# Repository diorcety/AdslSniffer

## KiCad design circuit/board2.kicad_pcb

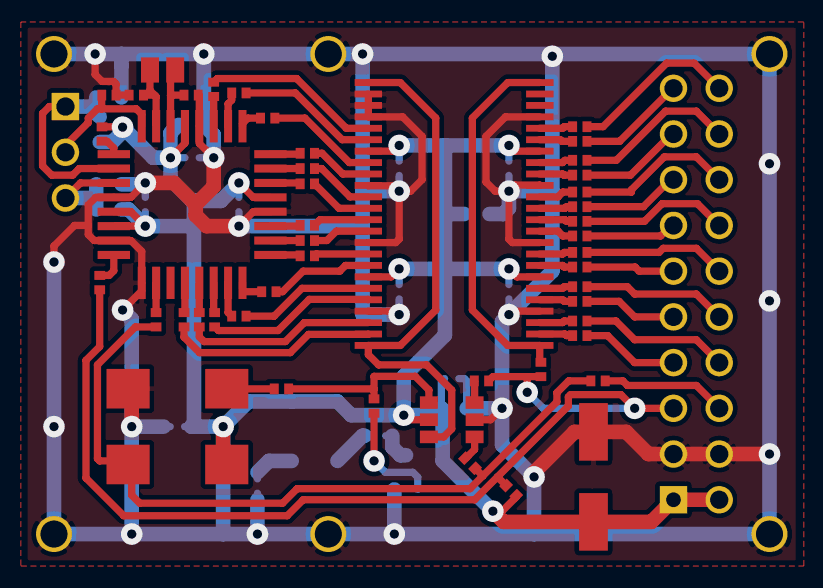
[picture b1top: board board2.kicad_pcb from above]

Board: 2 copper layers, 71 parts (0 on the bottom side), 79 nets.

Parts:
C1, C2, C3, C5, C6, C7, C8, C9, C10, C11, C12, C13: 100n; SM0402
C4, C15, C16, C18, C19: 10u; SM0805
C20: 100u; ESMT18
D1: LED PW; SM1206POL
D2: LED EN; SM1206POL
D3, D4, D5, D6: 3.3V; SOD523
P3: CONN_3; PIN_ARRAY_3X1
P4: CONN_20; pin_array_10x2
Q1: MOS_N; SOT323
R5, R47: 1k; SM0402
R6, R7, R8, R9, R10, R11, R12, R13, R14, R15, R16, R17, R18, R19: 33; SM0402
R20, R22, R23, R24, R25, R26, R46: 49; SM0402
R21, R30, R31, R32, R33, R34, R35, R36, R37, R38, R39, R40, R41, R42, R43: 100; SM0402
R44, R45: 47; SM0402
U1: ADC14L020; LQFP32
U2: 74L2G04; SOT23_6
U3: 74LS162374; SSOP48
X1: CMOS_OSCI; Sit7x5

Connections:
+3.3V: C5.1, C6.1, C7.1, C8.1, C9.1, C10.1, C11.1, C12.1, C13.1, C15.1, C16.1, C18.1, C19.1, C20.1, D1.1, D2.1, D3.2, D5.2, P4.1, P4.2, R5.2, R47.1, U1.5, U1.6, U1.21, U1.29, U2.5, U3.7, U3.18, U3.31, U3.42, X1.4
/CLK: P4.6, R21.1
/L_ENABLE: P4.5, R22.1, R23.1, R24.1, R47.2
GND: C1.2, C2.2, C3.2, C5.2, C6.2, C7.2, C8.2, C9.2, C10.2, C11.2, C12.2, C13.2, C15.2, C16.2, C18.2, C19.2, C20.2, D4.1, D6.1, P4.3, P4.4, Q1.S, R45.2, U1.4, U1.7, U1.9, U1.20, U1.28, U2.2, U3.4, U3.10, U3.15, U3.21, U3.26, U3.27, U3.28, U3.34, U3.39, U3.45, X1.2
unnamed: P4.12, R35.1
unnamed: P4.10, R33.1
unnamed: P4.20, R43.1
unnamed: P4.11, R34.1
unnamed: P4.13, R36.1
unnamed: P4.14, R37.1
unnamed: P4.15, R38.1
unnamed: P4.16, R39.1
unnamed: P4.17, R40.1
unnamed: P4.18, R41.1
unnamed: P4.19, R42.1
unnamed: P4.9, R32.1
unnamed: P4.8, R31.1
unnamed: P4.7, R30.1
unnamed: R25.2, R46.2, U2.4
unnamed: Q1.G, R46.1
unnamed: Q1.D, R44.1
unnamed: D1.2, R45.1
unnamed: D2.2, R44.2
unnamed: R5.1, U1.1
unnamed: R23.2, U2.3
unnamed: R22.2, U1.8
unnamed: R20.2, U1.10
unnamed: R25.1, X1.1
unnamed: R11.2, U1.17
unnamed: R16.2, U1.24
unnamed: R15.2, U1.23
unnamed: R14.2, U1.22
unnamed: R13.2, U1.19
unnamed: R12.2, U1.18
unnamed: R10.2, U1.16
unnamed: R9.2, U1.15
unnamed: R8.2, U1.14
unnamed: R7.2, U1.13
unnamed: C3.1, C4.1, U1.30
unnamed: R30.2, U3.2
unnamed: R31.2, U3.3
unnamed: R32.2, U3.5
unnamed: R33.2, U3.6
unnamed: R26.1, U2.1
unnamed: U2.6, U3.25, U3.48
unnamed: R34.2, U3.8
unnamed: R7.1, U3.46
unnamed: R41.2, U3.17
unnamed: R13.1, U3.37
unnamed: R12.1, U3.38
unnamed: R42.2, U3.19
unnamed: R14.1, U3.36
unnamed: R6.1, U3.47
unnamed: R6.2, U1.12
unnamed: R19.1, U3.29
unnamed: R19.2, U1.27
unnamed: R18.2, U1.26
unnamed: R17.2, U1.25
unnamed: R35.2, U3.9
unnamed: R43.2, U3.20
unnamed: R18.1, U3.30
unnamed: R11.1, U3.40
unnamed: R36.2, U3.11
unnamed: R10.1, U3.41
unnamed: R37.2, U3.12
unnamed: R17.1, U3.32
unnamed: R38.2, U3.13
unnamed: R16.1, U3.33
unnamed: R9.1, U3.43
unnamed: R39.2, U3.14
unnamed: R8.1, U3.44
unnamed: R15.1, U3.35
unnamed: R40.2, U3.16
unnamed: R24.2, U3.1, U3.24
unnamed: R20.1, R21.2, R26.2, X1.3
unnamed: C1.1, P3.2, U1.32
unnamed: C2.1, C4.2, U1.31
unnamed: D3.1, D4.2, P3.1, U1.2
unnamed: D5.1, D6.2, P3.3, U1.3

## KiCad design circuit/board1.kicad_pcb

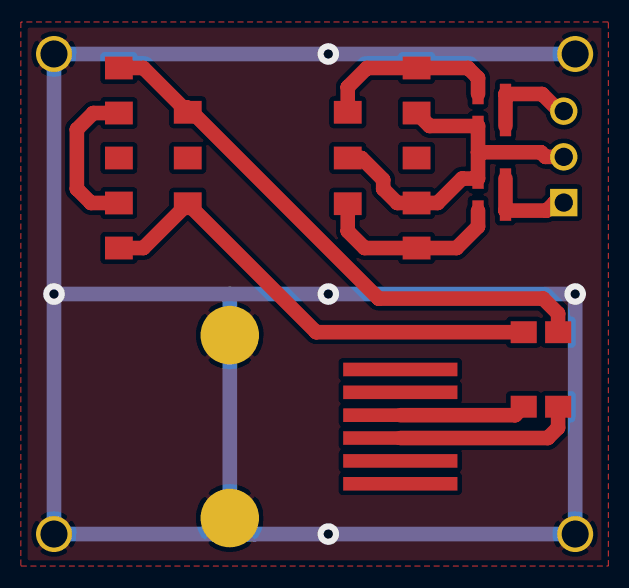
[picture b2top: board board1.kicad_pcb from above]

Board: 2 copper layers, 9 parts (0 on the bottom side), 11 nets.

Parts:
P1: RJ12; RJ11SMT
P2: CONN_3; PIN_ARRAY_3X1
R1, R2: 8k25; SM0603
R3, R4: 1k1; SM0603
T1: B0727-BL
T2: 1812DPS
T3: PWB2010L; PWB2010LB

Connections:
AGND: P1.7, P1.8
unnamed: P2.1, R2.2, R4.1
unnamed: R1.1, T1.6, T3.6
unnamed: R2.1, T1.10, T3.4
unnamed: P1.4, T2.4
unnamed: P2.3, R1.2, R3.1
unnamed: T1.2, T1.4
unnamed: T1.1, T2.3, T3.3
unnamed: P1.3, T2.1
unnamed: T1.5, T2.2, T3.1
unnamed: P2.2, R3.2, R4.2, T1.7, T1.9, T3.5

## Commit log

2012-01-12 Alignement connecteurs
2012-01-12 Correction positions resitances ADC
2012-01-13 Amelioration Schema
2012-01-31 Correction empreinte C4
2012-12-30 Utilise des connecteurs traversant (moins cher)
2012-12-30 Modifie l'emplacement et le net de P6
2012-12-30 Fix DRC
2012-12-30 Ajoute leds
2012-12-30 Ajoute condensateur 10u a chaque composant
2012-12-30 Corrige nom et ajoute csv des composants
2012-12-30 Ajoute transistor pour led en
2012-12-30 Ajout d'une resistance de pull-up pour EN
2012-12-30 Met le COMMON de V+ et V- au milieu
2012-12-31 Corrige empreintes/3D
2012-12-31 Recentre les circuits
2012-12-31 Reduction taille du circuit + nettoyages pistes
2012-12-31 Met a jour et corrige la liste des composants
2013-01-01 Supprime le composant contre surtension et le remplace par des zeners
2013-01-03 Utilise B0727-BLB et 1812DPS-472MLB Ajustement des resistances
2013-01-08 Utilise le meme condensateur pour les 10uF
2013-01-24 Start software part
2013-01-24 Reduce PCB size
2013-01-27 Ajoute l'empreinte de l'autre transformateur
2013-02-04 Change de package du capacitor 20 (can capacitor)
2013-02-04 Add fx2 doc
2013-02-04 Agrandi 2 vias
2013-02-04 Active PA.3 en sortie à 1 en idle et 0 en test
2013-02-05 Meilleur trace autour du condensateur
2013-02-14 Ameliore USB lib
2013-02-16 Amelioration API libUSB
2014-01-03 Improve silk layers and pin names on the PCB
2014-01-03 Improve silk layers again
2014-01-03 Circuit Multiple improvement
2014-01-03 Split the two parts
2014-01-04 Circuit: Add AGND and improve GND zone
2014-01-04 Update GND zone and add vias
2014-01-04 Add ON/En on bottom silk
2014-01-04 Update 10u capacitor BOM reference
2014-01-04 Add silk marker on diode footprint
2014-01-05 Split 2 board for production
2014-01-05 -Update fx2lib -Check sdcc tools in configure.ac
2014-01-05 Software: Add git ignore files
2014-01-05 Software: Fix lib and test
2014-01-05 Software: Fix typo and display
2014-01-06 Update fx2lib
2014-01-06 Calibrate the fx2 firmare to simulate board data send (correct frequency & data amount)
2014-01-08 Firmware: Prepare wareform Test: fix rate calculation
2014-01-09 Add GNURadio module
2014-01-09 Software: libUSB improve C++ wrapper
2014-01-12 Software: add functions to c++ wrapper
2014-01-13 Software: Improve lib & firmware -Add sample rate control command
2014-01-13 Software/GR: Add lib dependency
2014-01-15 Software: Continue gnuradio work
2014-01-15 Software: capture works with GR
2014-01-16 Software: working solution
2014-01-16 Software/GR: Wait for buffer in work method
2014-01-22 Prepare real usage
2014-01-26 Fix previous commit
2014-01-31 Fix RJ11 holes
2014-02-03 Add some comments about pins and add pictures of PCBs
2015-01-03 Fix compilation issues
2015-01-04 Firmware: Add deploy target
2015-01-04 Configure: Add switches (debug, strict)
2015-01-04 Test: Fix wait issue
2015-01-04 Indent all sources
